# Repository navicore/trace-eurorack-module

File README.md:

<!-- ghmig:moved -->
> **This repository has moved to [https://git.navicore.tech/navicore/trace-eurorack-module](https://git.navicore.tech/navicore/trace-eurorack-module).**
>
> The GitHub copy is archived and no longer maintained.

# Trace

**A DIY 24HP Eurorack Oscilloscope**

A custom 2-channel oscilloscope module designed for audio and CV visualization with persistent settings.

> **Project name**: Trace Eurorack Module (repository/development name)
> **Module name**: Trace

## Design Philosophy

- **Function over size pressure**: 24HP for comfortable viewing and control
- **Tactile controls**: Encoders and buttons for performance-friendly operation
- **Focused scope**: Audio rate and sub-audio CV visualization
- **No signal loading**: High impedance inputs, clean buffered passthroughs
- **Persistent settings**: Settings survive power cycles

## Specifications

### Physical
- **Width**: 24HP (121.92mm)
- **Display**: 4.3" SPI TFT (non-touch)
- **Controls**: 2 rotary encoders, 2-3 momentary buttons

### Electrical
- **Input Channels**: 2
- **Input Range**: ±12V (safe), ±5V typical
- **Input Impedance**: >100kΩ
- **Coupling**: DC-coupled
- **Passthrough**: 2 buffered outputs
- **Power**: Eurorack ±12V bus

### Processing
- **MCU**: RP2040 (Raspberry Pi Pico)
- **ADC**: 12-bit, 0-3.3V range
- **Sample Rate**: 10-50kSPS (audio + sub-audio)
- **Firmware**: Rust (rp-hal/embassy-rp)

## Repository Structure

```
/design/          - Schematics, PCB layouts, mechanical drawings
/docs/            - Design decisions, calculations, reference material
/firmware/        - Rust firmware source
/bom/             - Bill of materials, part sourcing
```

## Current Status

**Phase**: Initial design and planning

See `/docs/` for detailed design decisions.

## License

This project uses a dual-license approach:

- **Firmware/Software**: MIT License (see LICENSE-SOFTWARE)
- **Hardware Designs**: Creative Commons BY-SA 4.0 (see LICENSE-HARDWARE)

This follows the practice of open hardware projects.

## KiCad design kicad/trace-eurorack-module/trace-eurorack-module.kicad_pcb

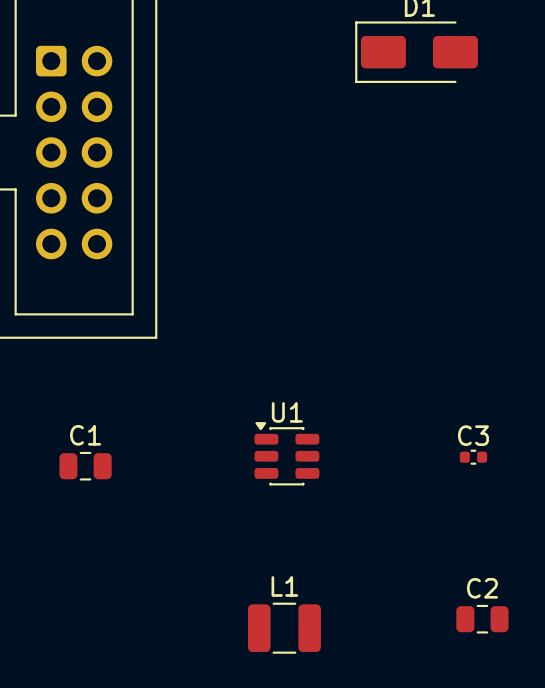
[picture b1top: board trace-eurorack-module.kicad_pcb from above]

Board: 2 copper layers, 7 parts (0 on the bottom side), 6 nets, no tracks yet.

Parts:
C1: 10uF; C_0805_2012Metric
C2: 22uF; C_0805_2012Metric
C3: 100nF; C_0402_1005Metric
D1: SS14; D_SMA
J1: Eurorack_Power; IDC-Header_2x05_P2.54mm_Vertical
L1: 10uH; L_1210_3225Metric
U1: AP63203WU-7; TSOT-23-6

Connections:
+3.3V: C2.1, L1.2, U1.1
+12V: C1.1, J1.9, J1.10, U1.2, U1.3
-12V_RAW: D1.1, J1.1
BST: C3.2, U1.6
GND: C1.2, C2.2, J1.2, J1.3, J1.4, J1.5, J1.6, J1.7, J1.8, U1.4
SW: C3.1, L1.1, U1.5

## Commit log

2025-12-07 kicad
2025-12-21 power
2025-12-21 save
2025-12-21 saved
2026-04-28 Repository moved to https://git.navicore.tech/navicore/trace-eurorack-module
